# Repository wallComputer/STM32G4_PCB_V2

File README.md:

# STM32G4_PCB_V2
 Breakout Board for STM32G431CBU6

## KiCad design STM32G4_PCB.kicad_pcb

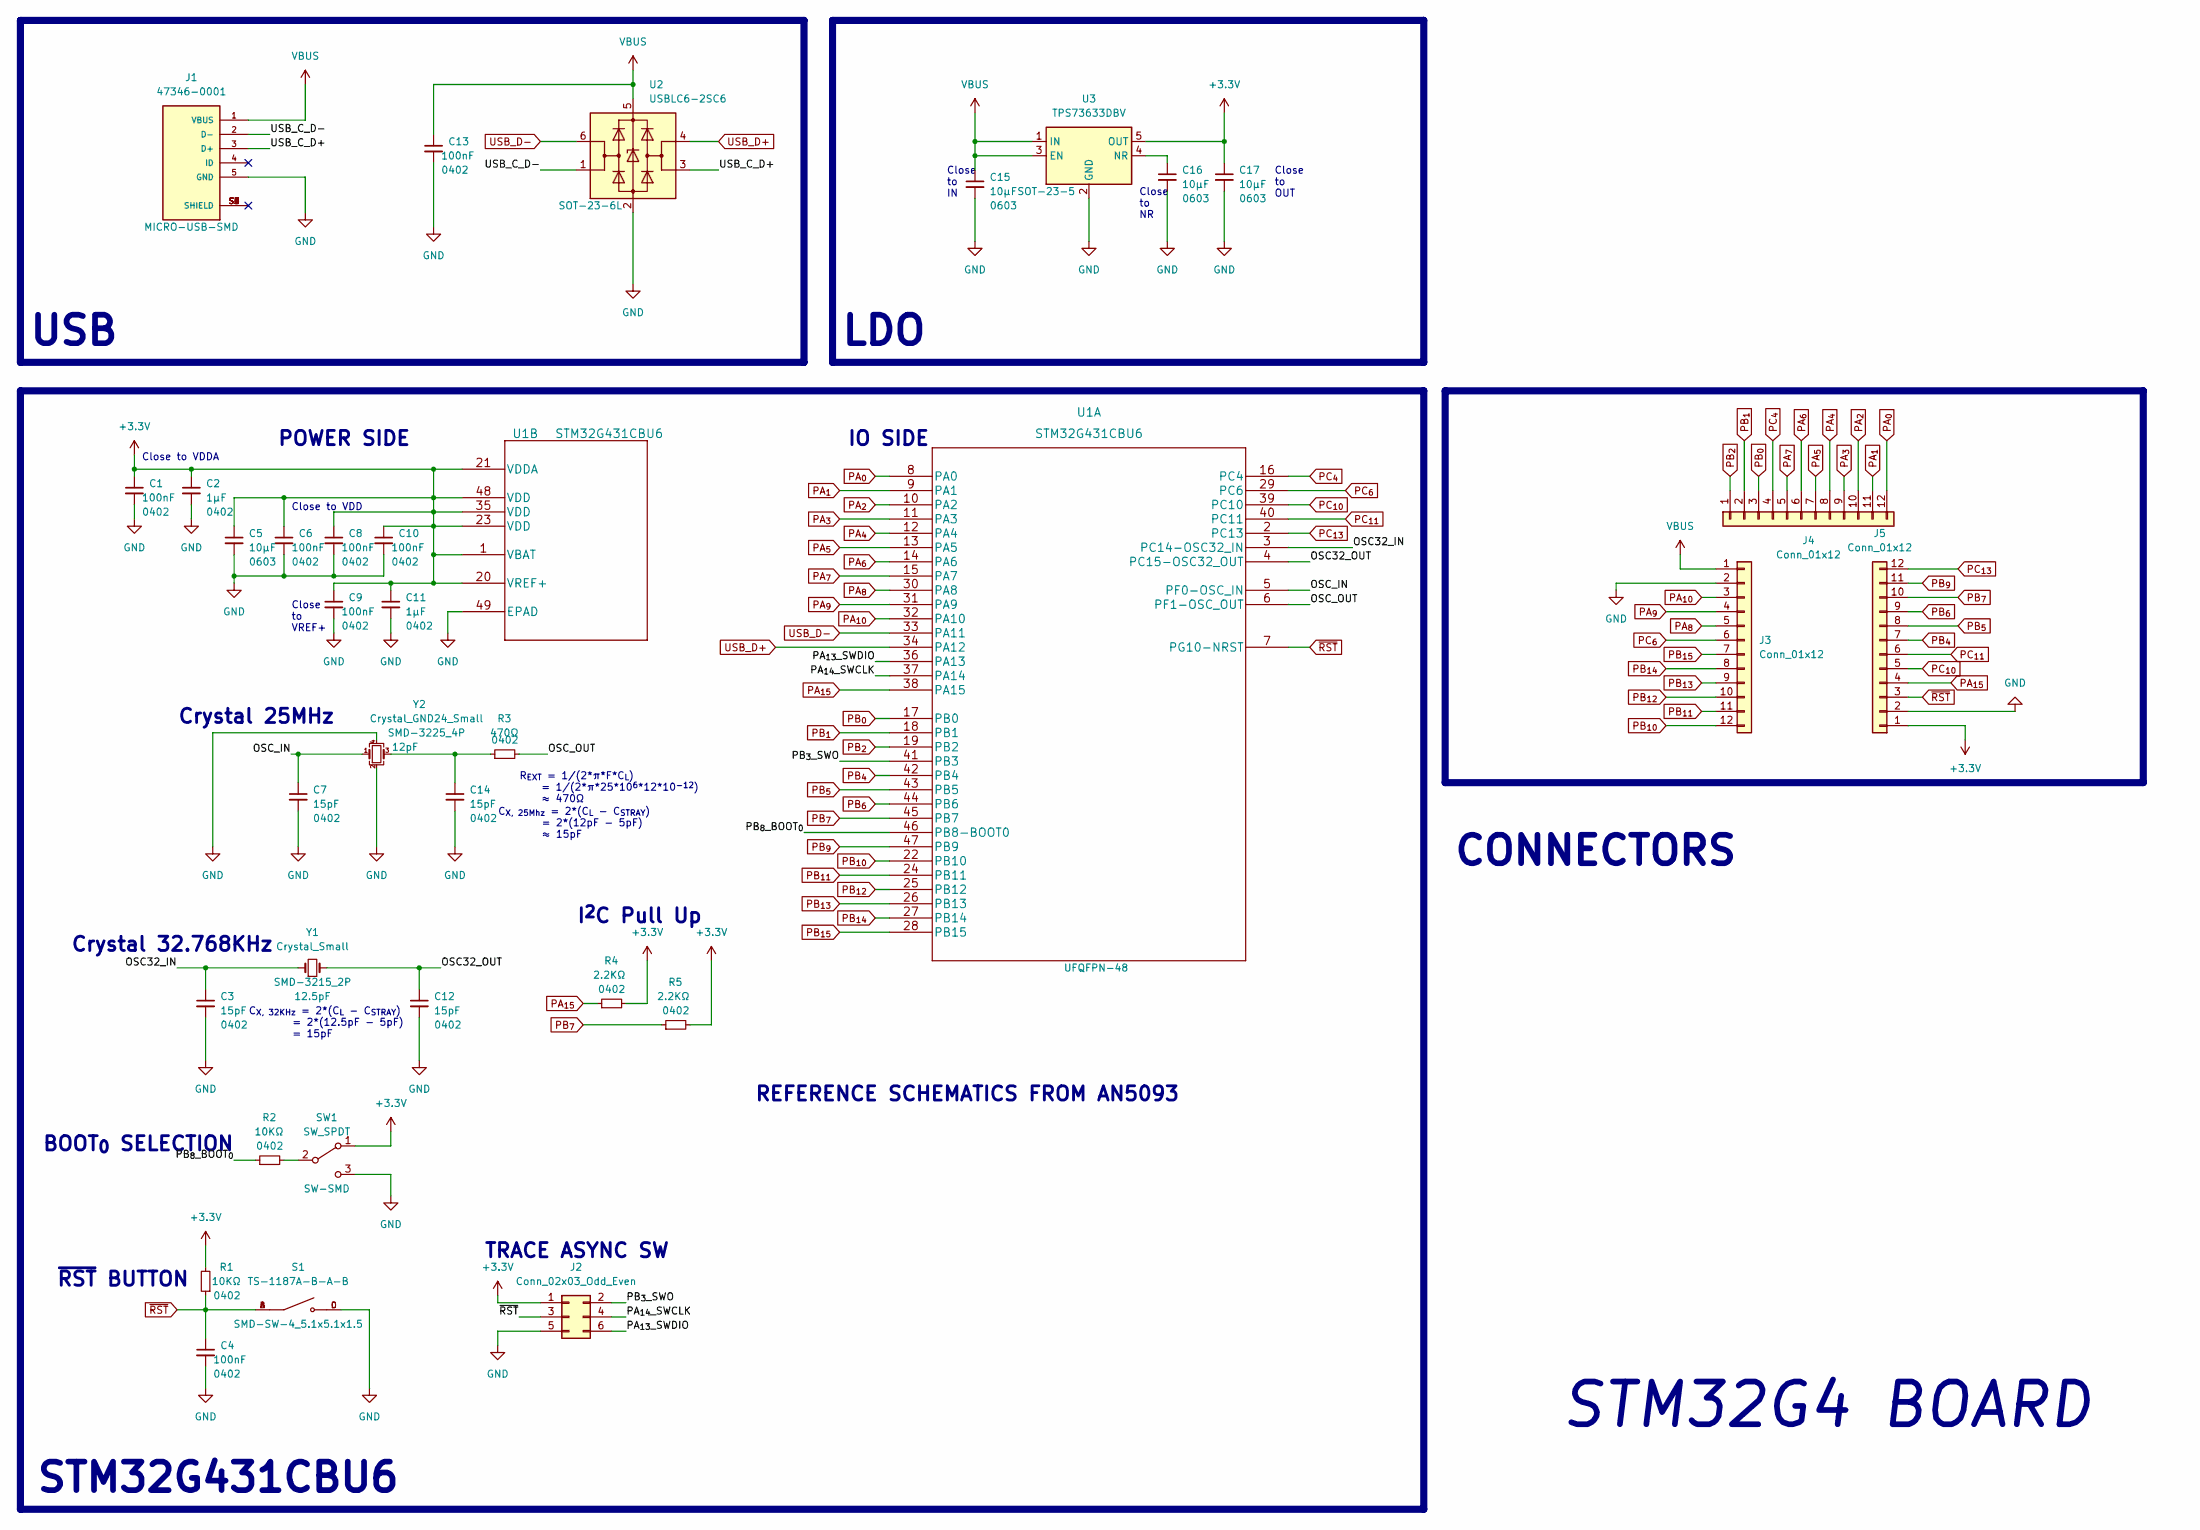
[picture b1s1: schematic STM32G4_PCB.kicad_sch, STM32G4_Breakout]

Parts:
C1, C4, C6, C8, C9, C10, C13: 100nF; C_0402_1005Metric; JLC 0402
C2, C11: 1µF; C_0402_1005Metric; JLC 0402
C3, C7, C12, C14: 15pF; C_0402_1005Metric; JLC 0402
C5, C15, C16, C17: 10µF; C_0603_1608Metric; JLC 0603
J1: 47346-0001; MOLEX_47346-0001; PARTREV E; JLC MICRO-USB-SMD
J2: Conn_02x03_Odd_Even; PinSocket_2x03_P2.54mm_Vertical
J3, J4, J5: Conn_01x12; PinHeader_1x12_P2.54mm_Vertical
R1, R2: 10KΩ; R_0402_1005Metric; JLC 0402
R3: 470Ω; R_0402_1005Metric; JLC 0402
R4, R5: 2.2KΩ; R_0402_1005Metric; JLC 0402
S1: TS-1187A-B-A-B; SW_TS-1187A-B-A-B; PARTREV A0; JLC SMD-SW-4_5.1x5.1x1.5
SW1: SW_SPDT; SW_SPDT_PCM12; JLC SW-SMD
U1: STM32G431CBU6; JLC UFQFPN-48
U2: USBLC6-2SC6; SOT-23-6; JLC SOT-23-6L
U3: TPS73633DBV; SOT-23-5; JLC SOT-23-5
Y1: Crystal_Small; Crystal_SMD_3215-2Pin_3.2x1.5mm; JLC SMD-3215_2P
Y2: Crystal_GND24_Small; Crystal_SMD_3225-4Pin_3.2x2.5mm; JLC SMD-3225_4P

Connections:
+3V3: C1.1, C2.1, C5.1, C6.1, C8.1, C9.1, C10.1, C11.1, C17.1, J2.1, J5.1, R1.2, R4.2, R5.2, SW1.1 (A), U1.1 (VBAT), U1.20 (VREF+), U1.21 (VDDA), U1.23 (VDD), U1.35 (VDD), U1.48 (VDD), U3.5 (OUT)
/OSC32_IN: C3.1, U1.3 (PC14-OSC32_IN), Y1.1
/OSC32_OUT: C12.1, U1.4 (PC15-OSC32_OUT), Y1.2
/OSC_IN: C7.1, U1.5 (PF0-OSC_IN), Y2.1
/OSC_OUT: R3.2, U1.6 (PF1-OSC_OUT)
/PA_{13}_SWDIO: J2.6, U1.36 (PA13)
/PA_{14}_SWCLK: J2.4, U1.37 (PA14)
/PB_{3}_SWO: J2.2, U1.41 (PB3)
/PB_{8}_BOOT_{0}: R2.1, U1.46 (PB8-BOOT0)
/USB_C_D+: J1.3 (D+), U2.3 (I/O2)
/USB_C_D-: J1.2 (D-), U2.1 (I/O1)
GND: C1.2, C2.2, C3.2, C4.2, C5.2, C6.2, C7.2, C8.2, C9.2, C10.2, C11.2, C12.2, C13.2, C14.2, C15.2, C16.2, C17.2, J1.5 (GND), J2.5, J3.2, J5.2, S1.C, S1.D, SW1.3 (C), U1.49 (EPAD), U2.2 (GND), U3.2 (GND), Y2.2, Y2.4
unnamed: C14.1, R3.1, Y2.3
unnamed: C16.1, U3.4 (NR)
unnamed: R2.2, SW1.2 (B)
PA_{0}: J4.12, U1.8 (PA0)
PA_{1}: J4.11, U1.9 (PA1)
PA_{2}: J4.10, U1.10 (PA2)
PA_{3}: J4.9, U1.11 (PA3)
PA_{4}: J4.8, U1.12 (PA4)
PA_{5}: J4.7, U1.13 (PA5)
PA_{6}: J4.6, U1.14 (PA6)
PA_{7}: J4.5, U1.15 (PA7)
PA_{8}: J3.5, U1.30 (PA8)
PA_{9}: J3.4, U1.31 (PA9)
PA_{10}: J3.3, U1.32 (PA10)
PA_{15}: J5.4, R4.1, U1.38 (PA15)
PB_{0}: J4.3, U1.17 (PB0)
PB_{1}: J4.2, U1.18 (PB1)
PB_{2}: J4.1, U1.19 (PB2)
PB_{4}: J5.7, U1.42 (PB4)
PB_{5}: J5.8, U1.43 (PB5)
PB_{6}: J5.9, U1.44 (PB6)
PB_{7}: J5.10, R5.1, U1.45 (PB7)
PB_{9}: J5.11, U1.47 (PB9)
PB_{10}: J3.12, U1.22 (PB10)
PB_{11}: J3.11, U1.24 (PB11)
PB_{12}: J3.10, U1.25 (PB12)
PB_{13}: J3.9, U1.26 (PB13)
PB_{14}: J3.8, U1.27 (PB14)
PB_{15}: J3.7, U1.28 (PB15)
PC_{4}: J4.4, U1.16 (PC4)
PC_{6}: J3.6, U1.29 (PC6)
PC_{10}: J5.5, U1.39 (PC10)
PC_{11}: J5.6, U1.40 (PC11)
PC_{13}: J5.12, U1.2 (PC13)
USB_D+: U1.34 (PA12), U2.4 (I/O2)
USB_D-: U1.33 (PA11), U2.6 (I/O1)
VBUS: C13.1, C15.1, J1.1 (VBUS), J3.1, U2.5 (VBUS), U3.1 (IN), U3.3 (EN)
~RST: C4.1, J2.3, J5.3, R1.1, S1.A, S1.B, U1.7 (PG10-NRST)

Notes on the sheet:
LDO
USB
C_{X, 25Mhz} = 2*(C_{L} - C_{STRAY}) = 2*(12pF - 5pF) ≈ 15pF
STM32G4 BOARD
IO SIDE
POWER SIDE
BOOT_{0} SELECTION
Close to NR
STM32G431CBU6
I^{2}C Pull Up
Close to VDDA
~{RST} BUTTON
CONNECTORS
Close to OUT
Crystal 25MHz
Close to VREF+
TRACE ASYNC SW
Close to VDD
Crystal 32.768KHz
Close to IN
R_{EXT} = 1/(2*π*F*C_{L}) = 1/(2*π*25*10^{6}*12*10^{-12}) ≈ 470Ω
REFERENCE SCHEMATICS FROM AN5093
C_{X, 32KHz} = 2*(C_{L} - C_{STRAY}) = 2*(12.5pF - 5pF) = 15pF

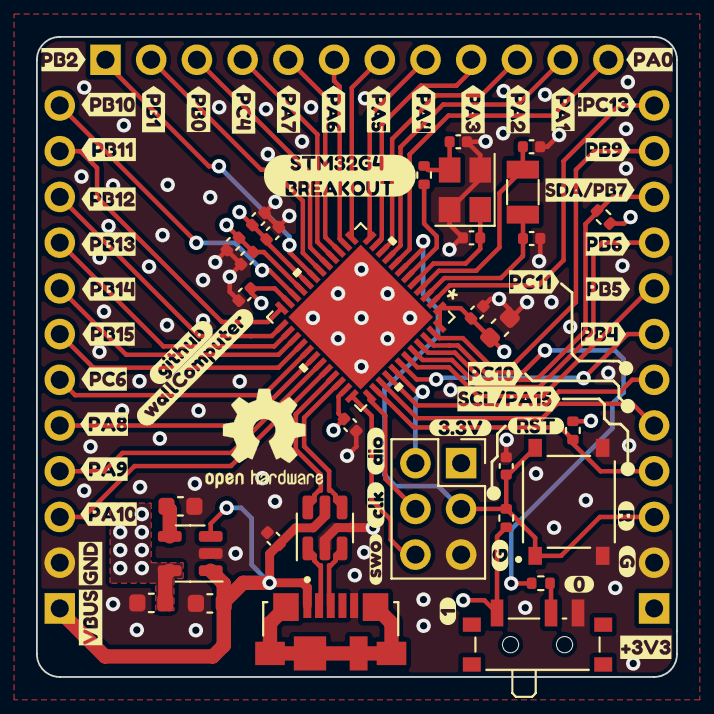
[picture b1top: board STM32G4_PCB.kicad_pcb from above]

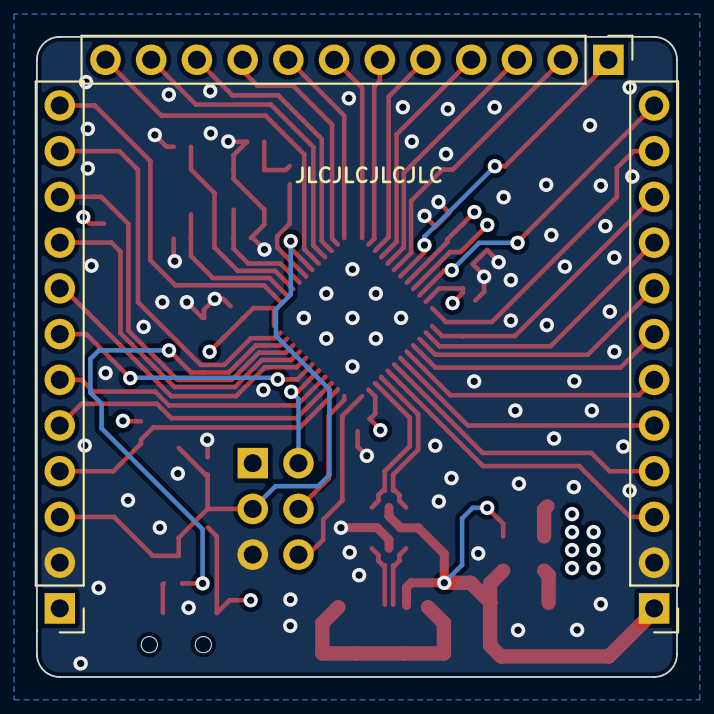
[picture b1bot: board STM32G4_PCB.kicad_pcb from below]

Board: 4 copper layers, 35.6 x 35.6 mm, 81 parts (3 on the bottom side), 50 nets.

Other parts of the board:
kibuzzard-625C2A9D: G***; kibuzzard-625C2A9D
kibuzzard-625C2AA9: G***; kibuzzard-625C2AA9
kibuzzard-625C2F2F: G***; kibuzzard-625C2F2F
kibuzzard-625C321F: G***; kibuzzard-625C321F
kibuzzard-625C332D: G***; kibuzzard-625C332D
kibuzzard-625C3253: G***; kibuzzard-625C3253
kibuzzard-625C3321: G***; kibuzzard-625C3321
kibuzzard-625C3326: G***; kibuzzard-625C3326
kibuzzard-625C3562: G***; kibuzzard-625C3562
kibuzzard-625EA97F: G***; kibuzzard-625EA97F
kibuzzard-625EA961: G***; kibuzzard-625EA961
kibuzzard-625EAB2F: G***; kibuzzard-625EAB2F
kibuzzard-625EAB9B: G***; kibuzzard-625EAB9B
kibuzzard-625EAB72: G***; kibuzzard-625EAB72
kibuzzard-625EAB92: G***; kibuzzard-625EAB92
kibuzzard-625EABA6: G***; kibuzzard-625EABA6
kibuzzard-625EABB3: G***; kibuzzard-625EABB3
kibuzzard-625EABC2: G***; kibuzzard-625EABC2
kibuzzard-625EABD7: G***; kibuzzard-625EABD7
kibuzzard-625EABEB: G***; kibuzzard-625EABEB
kibuzzard-625EAC54: G***; kibuzzard-625EAC54
kibuzzard-625EAC98: G***; kibuzzard-625EAC98
kibuzzard-625EACF4: G***; kibuzzard-625EACF4
kibuzzard-625EB0F6: G***; kibuzzard-625EB0F6
kibuzzard-625EB1FB: G***; kibuzzard-625EB1FB
kibuzzard-625EB2AC: G***; kibuzzard-625EB2AC
kibuzzard-625EB2BE: G***; kibuzzard-625EB2BE
kibuzzard-625EB3ED: G***; kibuzzard-625EB3ED
kibuzzard-625EB11D: G***; kibuzzard-625EB11D
kibuzzard-625EB17A: G***; kibuzzard-625EB17A
kibuzzard-625EB29C: G***; kibuzzard-625EB29C
kibuzzard-625EB36F: G***; kibuzzard-625EB36F
kibuzzard-625EB109: G***; kibuzzard-625EB109
kibuzzard-625EB131: G***; kibuzzard-625EB131
kibuzzard-625EB149: G***; kibuzzard-625EB149
kibuzzard-625EB164: G***; kibuzzard-625EB164
kibuzzard-625EB275: G***; kibuzzard-625EB275
kibuzzard-625EB353: G***; kibuzzard-625EB353
kibuzzard-625EDF71, kibuzzard-625EDF71#2: G***; kibuzzard-625EDF71
kibuzzard-625EF5DE: G***; kibuzzard-625EF5DE
kibuzzard-625EF7B7: G***; kibuzzard-625EF7B7
kibuzzard-625EF74A: G***; kibuzzard-625EF74A
kibuzzard-625EF765: G***; kibuzzard-625EF765
kibuzzard-625F2D40: G***; kibuzzard-625F2D40
kibuzzard-625F32F4: G***; kibuzzard-625F32F4
kibuzzard-625F331C: G***; kibuzzard-625F331C

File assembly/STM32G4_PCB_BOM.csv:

Comment,Designator,Footprint,LCSC
"100nF","C1,C4,C6,C8,C9,C10,C13","Capacitor_SMD:C_0402_1005Metric","C1525"
"1µF","C2,C11","Capacitor_SMD:C_0402_1005Metric","C52923"
"15pF","C3,C7,C12,C14","Capacitor_SMD:C_0402_1005Metric","C1548"
"10µF","C5,C15,C16,C17","Capacitor_SMD:C_0603_1608Metric","C19702"
"47346-0001","J1","MOLEX_473460001:MOLEX_47346-0001","C132560"
"Conn_02x03_Odd_Even","J2","Connector_PinSocket_2.54mm:PinSocket_2x03_P2.54mm_Vertical",""
"Conn_01x12","J3,J4,J5","Connector_PinHeader_2.54mm:PinHeader_1x12_P2.54mm_Vertical",""
"10KΩ","R1,R2","Resistor_SMD:R_0402_1005Metric","C25744"
"470Ω","R3","Resistor_SMD:R_0402_1005Metric","C25117"
"2.2KΩ","R4,R5","Resistor_SMD:R_0402_1005Metric","C25879"
"TS-1187A-B-A-B","S1","TS-1187A-B-A-B:SW_TS-1187A-B-A-B","C318884"
"SW_SPDT","SW1","Button_Switch_SMD:SW_SPDT_PCM12","C963206"
"STM32G431CBU6","U1","STM32G431CBU6:STM32G431CBU6","C529356"
"USBLC6-2SC6","U2","Package_TO_SOT_SMD:SOT-23-6","C7519"
"TPS73633DBV","U3","Package_TO_SOT_SMD:SOT-23-5","C28038"
"Crystal_Small","Y1","Crystal:Crystal_SMD_3215-2Pin_3.2x1.5mm","C32346"
"Crystal_GND24_Small","Y2","Crystal:Crystal_SMD_3225-4Pin_3.2x2.5mm","C9006"

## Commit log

2022-04-19 Delete STM32G4_PCB-backups directory
    Removed backups
2022-04-19 Delete #auto_saved_files#
    Delete autosave location
2022-04-19 Delete .DS_Store
    Remove unknown file.
2022-04-19 Delete .DS_Store
    Remove unknown file
2022-04-19 Delete STM32G4_PCB.round-tracks-config
    Remove experimental file
2022-04-19 Delete _autosave-STM32G4_PCB.kicad_sch
    Delete autosave file

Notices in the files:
parts and their libraries:
Copyright 2021 Accelerated Designs. All rights reserved.
